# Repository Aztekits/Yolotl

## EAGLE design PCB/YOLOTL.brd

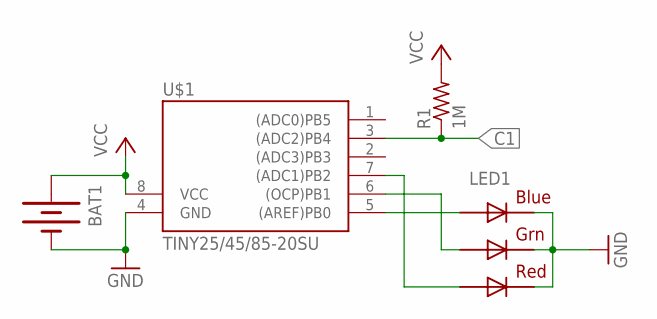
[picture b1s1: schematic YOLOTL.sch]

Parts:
BAT1: BATTERY20PTH; BATTCOM_20MM_PTH
LED1: RGBLED5050
R1: 1M; R1206
U$1: TINY25/45/85-20SU; SOIC8

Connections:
C1: R1.1, U$1.3 ((ADC2)PB4)
GND: BAT1.2 (-), LED1.4 (BLUE_C), LED1.5 (RED_C), LED1.6 (GREEN_C), U$1.4 (GND)
unnamed: LED1.2 (RED_A), U$1.7 ((ADC1)PB2)
unnamed: LED1.3 (BLUE_A), U$1.5 ((AREF)PB0)
unnamed: LED1.1 (GREEN_A), U$1.6 ((OCP)PB1)
VCC: BAT1.1 (+), R1.2, U$1.8 (VCC)

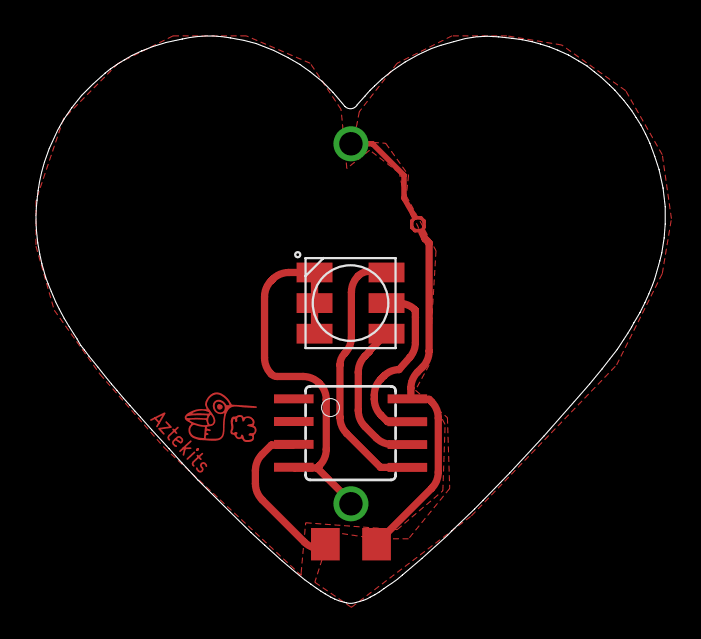
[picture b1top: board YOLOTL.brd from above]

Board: 2 copper layers, 35.0 x 31.5 mm, 4 parts (1 on the bottom side), 6 nets.

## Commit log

2014-02-03 Primera version
    Funciones ritmicas habilitadas, modo sleep para ahorro de energia y
    reactivacion por interrupción.
2014-02-04 Corrección de Interrupción
    Se desabilitaron interrupcioens en funcionamiento normal, y se
    desabilitan al no haber detección de contacto para poder acceder a modo
    sleep. Desabilitando nuevamente al despertar.
2014-02-13 Diseño electrónico agregado
    PCB y esquemas en su última versión.

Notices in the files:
parts and their libraries:
SparkFun: Licensing: CC v3.0 Share-Alike You are welcome to use this library for commercial purposes.
